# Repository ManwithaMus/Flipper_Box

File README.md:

Flipper Box/IR Breakout Board KiCad design files

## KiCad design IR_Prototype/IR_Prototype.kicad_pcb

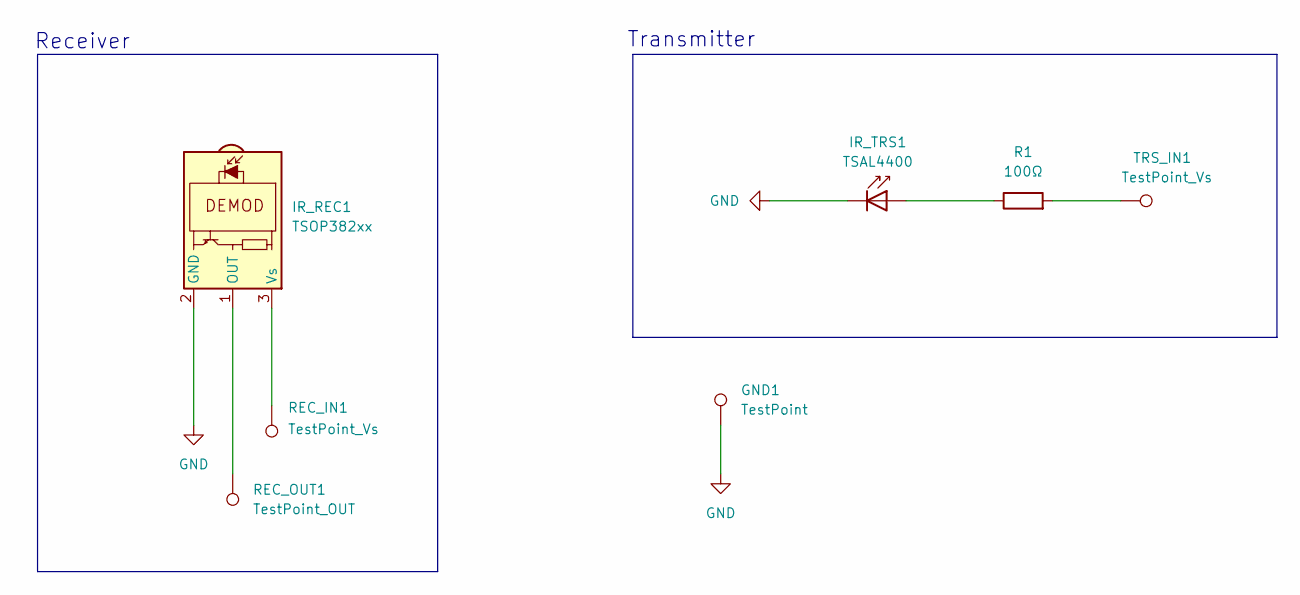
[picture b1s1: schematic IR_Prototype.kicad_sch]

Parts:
GND1: TestPoint; TestPoint_Plated_Hole_D2.0mm
IR_REC1: TSOP382xx; Vishay_MINICAST-3Pin
IR_TRS1: TSAL4400; LED_D3.0mm_IRBlack
R1: 100Ω; R_Axial_DIN0207_L6.3mm_D2.5mm_P10.16mm_Horizontal
REC_IN1: TestPoint_Vs; TestPoint_Plated_Hole_D2.0mm
REC_OUT1: TestPoint_OUT; TestPoint_Plated_Hole_D2.0mm
TRS_IN1: TestPoint_Vs; TestPoint_Plated_Hole_D2.0mm

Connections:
GND: GND1.1, IR_REC1.2 (GND), IR_TRS1.1 (K)
unnamed: IR_REC1.1 (OUT), REC_OUT1.1
unnamed: IR_REC1.3 (Vs), REC_IN1.1
unnamed: IR_TRS1.2 (A), R1.1
unnamed: R1.2, TRS_IN1.1

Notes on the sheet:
Receiver
Transmitter

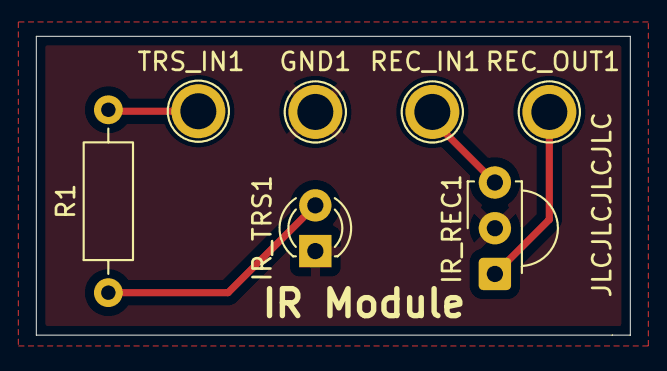
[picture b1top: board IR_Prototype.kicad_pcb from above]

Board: 4 copper layers, 33.0 x 16.6 mm, 7 parts (0 on the bottom side), 5 nets.
